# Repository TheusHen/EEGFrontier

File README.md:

# EEGFrontier V2

> [!CAUTION]
> **THIS BRANCH IS OUTDATED – DO NOT FABRICATE THIS BOARD!**
> The design files in this `v2` branch are outdated and contain known hardware issues. A new version is currently under active development. **Under no circumstances should you manufacture or order PCBs from this branch.** Please wait for the official update and release.

EEGFrontier is an open-source EEG acquisition platform built around Texas Instruments ADS1299 and the Seeed XIAO RP2040.

This repository includes:
- Hardware design files (KiCad)
- Firmware (PlatformIO / Arduino)
- Project assets and documentation images
- Host software (`Pendulum`)

## Current Status

This branch introduces the **V2 PCB** update:
- Migration to **ADS1299IPAGR** and **8 EEG channels**
- PCB rework focused on lower noise
- Curved routing for cleaner analog signal paths
- Revised GND strategy (less direct GND trace routing in sensitive analog areas)

Still pending on V2:
- BOM update
- Firmware update and validation for the new hardware revision

## V1 vs V2 Snapshot

| Topic | V1 | V2 |
|---|---|---|
| Analog front-end | ADS1299-4PAGR (4 channels) | ADS1299IPAGR (8 channels) |
| PCB routing style | Conventional routing | Curved tracks and analog cleanup |
| Noise-focused changes | Baseline | GND/routing revisions to reduce coupling and noise |

## Visual Comparison

### 3D View (Front)

| V1 | V2 |
|---|---|
|  |  |

### 3D View (Back)

| V1 | V2 |
|---|---|
|  |  |

### PCB Layout

| V1 | V2 |
|---|---|
|  |  |

### Schematic

| V1 | V2 |
|---|---|
|  |  |

## Project Concept

The board connects dry electrodes and streams real-time EEG data to a computer over USB for analysis and visualization.
The main objective is practical learning: open hardware + open firmware + transparent signal chain.

## Quick Start

1. Flash the firmware to the Seeed XIAO RP2040 using PlatformIO.
2. Connect the EEGFrontier board via USB.
3. Attach EEG electrodes (channels, REF, BIAS).
4. Open Pendulum or a serial monitor.
5. Start streaming with the `START` command.

## Hardware Highlights (V2)

- ADS1299IPAGR-based 8-channel EEG analog front-end
- Seeed XIAO RP2040 as main controller
- Input header for EEG channels + reference + bias
- Start button input (`BTN_START`)
- Status LEDs (power and stream/activity)
- Compact two-layer PCB with revised analog routing decisions

## Firmware Overview

The firmware in `firmware/` currently provides:
- ADS1299 initialization and register configuration
- DRDY interrupt-based sampling
- Binary streaming protocol (COBS + CRC16)
- CSV debug mode
- Serial commands for diagnostics and control
- Recovery logic for acquisition timeout
- Self-test and lead-off diagnostics

Note: firmware behavior and defaults still need full alignment with the V2 hardware revision.

## Firmware Build (PlatformIO)

```bash
cd firmware
pio run -e xiao_rp2040
```

Monitor (default baud rate `921600`):

```bash
cd firmware
pio device monitor -b 921600
```

## Serial Commands (Firmware)

- `HELP`
- `INFO`
- `STATS`
- `REGS`
- `START`
- `STOP`
- `MODE BIN`
- `MODE CSV`
- `REINIT`
- `TEST ON`
- `TEST OFF`
- `SELFTEST`
- `LOFF ON`
- `LOFF OFF`
- `LOFF STATUS`
- `PING`

## Technical Specifications

- Channels: 8 EEG channels + REF + BIAS (V2 target)
- ADC: 24-bit (ADS1299 family)
- Sampling rate: configurable (up to ADS1299 limits)
- Interface: USB (CDC)
- Power: USB 5V

## Repository Structure

- `firmware/` - PlatformIO firmware for XIAO RP2040 + ADS1299
- `assets/` - Images used in this README
- `bom/` - Bill of Materials and pricing references
- `EEGFrontier.kicad_sch` / `EEGFrontier.kicad_pcb` - KiCad project files
- `Pendulum/` - Host software suite (**OUTDATED for V2 / 8 channels**)

## Pendulum (OUTDATED)

Outdated status:
- The current `Pendulum` implementation is still aligned with the previous channel configuration.
- It needs to be updated to fully support the V2 hardware changes (8 channels via ADS1299IPAGR).

For now, `Pendulum/README.md` should be treated as historical reference until the 8-channel update is done.

## Manufacturing Recommendation

Fully hand-soldering this board is not recommended.

The design uses fine-pitch components and sensitive analog circuitry. Prefer full assembly from a professional PCB assembly service (for example, JLCPCB), then hand-solder only unavoidable missing parts if necessary.

## Safety and Protection

Important safety notice:

This device interfaces electrically with the human body and must be used with caution.

- This project does not include medical-grade isolation.
- Never connect it to mains-powered equipment without proper USB isolation.
- Always operate with a battery-powered computer or a biomedical USB isolator.
- Do not use if the board, cables, or electrodes are damaged.
- Do not use on individuals with implanted electronic devices (for example, pacemakers).
- This project is for research, education, and experimentation only.

The author assumes no responsibility for misuse, unsafe assembly, or unsafe operation.

## Medical Disclaimer

This project is not a medical device and is not intended for diagnosis, treatment, or clinical use.

Any produced data is experimental and for education/research use only.

## Known Limitations

- No medical-grade isolation
- No onboard battery
- Susceptible to motion artifacts with dry electrodes
- Requires external software for filtering and analysis (for example, Pendulum)
- V2 BOM and firmware migration are still in progress
- Pendulum host software is outdated and still pending migration to 8 channels

## License

This project is released under the MIT License.
See `LICENSE` for details.

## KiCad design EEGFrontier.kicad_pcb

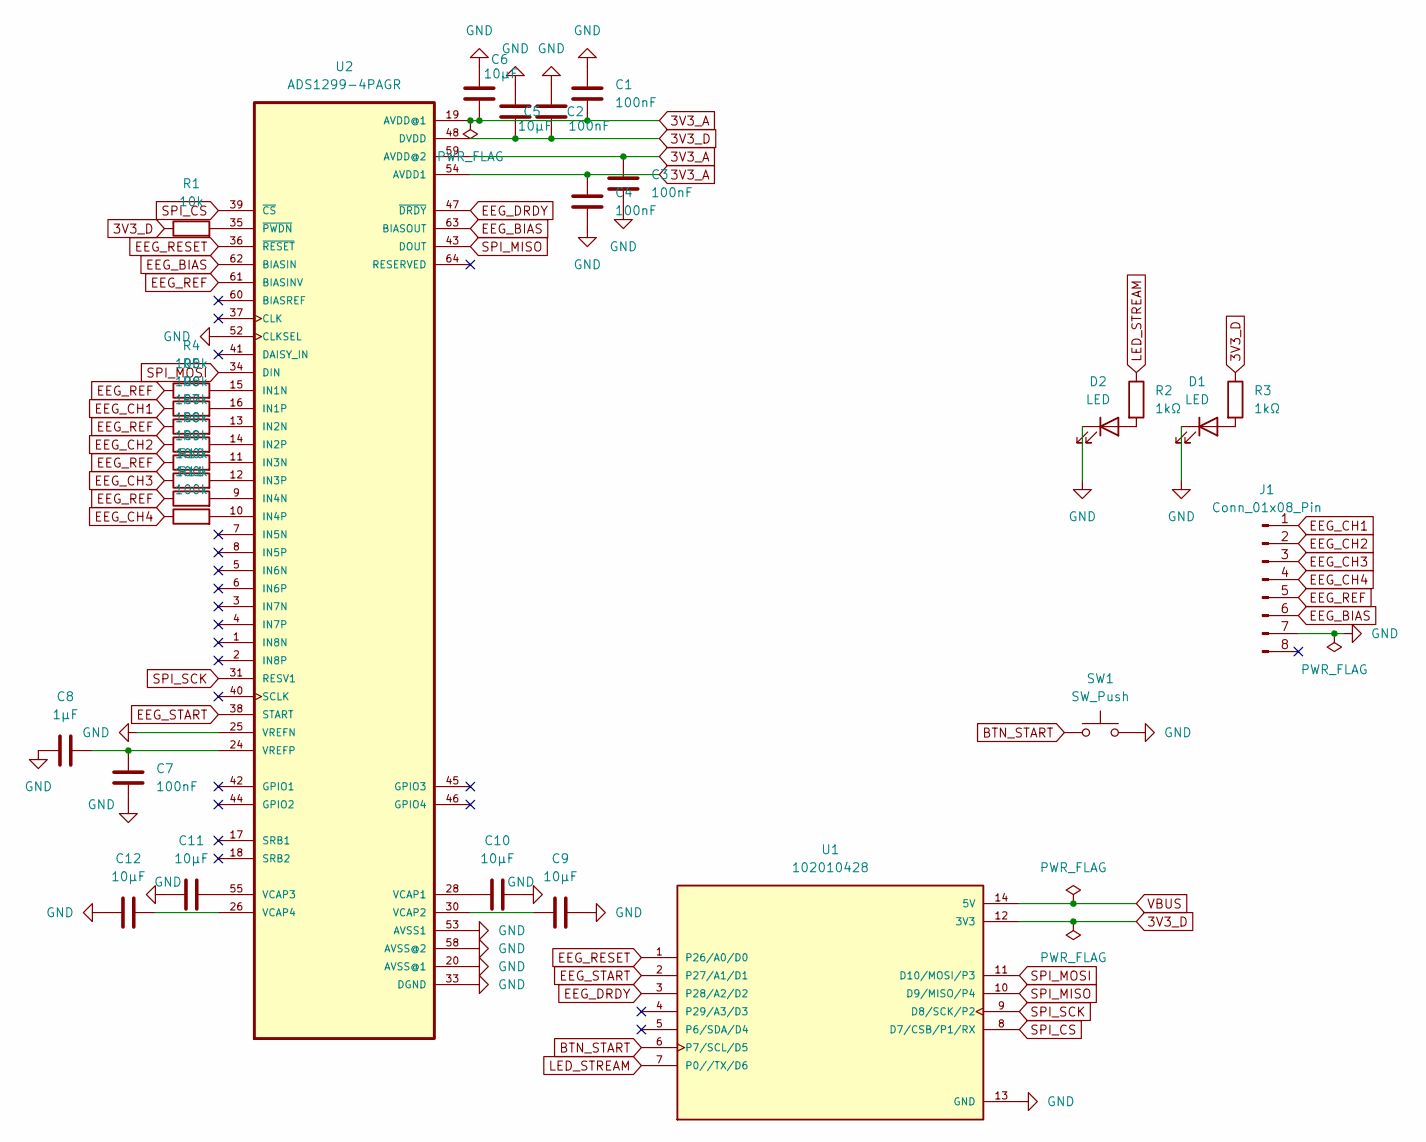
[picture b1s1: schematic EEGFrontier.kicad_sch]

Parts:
C1, C2, C3, C4, C7: 100nF; C_0603_1608Metric
C5, C6, C9, C10, C11, C12: 10µF; C_1206_3216Metric
C8: 1µF; C_0603_1608Metric
D1, D2: LED; LED_0805_2012Metric
J1: Conn_01x08_Pin; PinHeader_1x08_P2.54mm_Horizontal
R1: 10k; R_0805_2012Metric
R2, R3: 1kΩ; R_0805_2012Metric
R4, R5, R6, R7, R8, R9, R10, R11: 100k; R_0805_2012Metric
SW1: SW_Push; SW_Push_SPST_NO_Alps_SKRK
U1: 102010428; MODULE_102010428; PARTREV 1.3
U2: ADS1299-4PAGR; QFP50P1200X1200X120-64N

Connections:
3V3_A: C1.1, C3.2, C4.2, C6.1, U2.19 (AVDD@1), U2.21 (AVDD@1), U2.22 (AVDD@1), U2.54 (AVDD1), U2.56 (AVDD@1), U2.59 (AVDD@2)
3V3_D: C2.1, C5.1, R1.1, R3.1, U1.12 (3V3), U2.48 (DVDD), U2.50 (DVDD)
BTN_START: SW1.1, U1.6 (P7/SCL/D5)
EEG_BIAS: J1.6, U2.62 (BIASIN), U2.63 (BIASOUT)
EEG_CH1: J1.1, R5.1
EEG_CH2: J1.2, R7.1
EEG_CH3: J1.3, R9.1
EEG_CH4: J1.4, R11.1
EEG_DRDY: U1.3 (P28/A2/D2), U2.47 (~DRDY)
EEG_REF: J1.5, R4.1, R6.1, R8.1, R10.1, U2.61 (BIASINV)
EEG_RESET: U1.1 (P26/A0/D0), U2.36 (~RESET)
EEG_START: U1.2 (P27/A1/D1), U2.38 (START)
GND: C1.2, C2.2, C3.1, C4.1, C5.2, C6.2, C7.2, C8.2, C9.2, C10.2, C11.2, C12.2, D1.1 (K), D2.1 (K), J1.7, SW1.2, U1.13 (GND), U2.20 (AVSS@1), U2.23 (AVSS@1), U2.25 (VREFN), U2.32 (AVSS@1), U2.33 (DGND), U2.49 (DGND), U2.51 (DGND), U2.52 (CLKSEL), U2.53 (AVSS1), U2.57 (AVSS@1), U2.58 (AVSS@2)
LED_STREAM: R2.1, U1.7 (P0//TX/D6)
unnamed: D1.2 (A), R3.2
unnamed: D2.2 (A), R2.2
unnamed: R4.2, U2.15 (IN1N)
unnamed: R5.2, U2.16 (IN1P)
unnamed: R6.2, U2.13 (IN2N)
unnamed: R7.2, U2.14 (IN2P)
unnamed: R8.2, U2.11 (IN3N)
unnamed: R9.2, U2.12 (IN3P)
unnamed: R10.2, U2.9 (IN4N)
unnamed: R11.2, U2.10 (IN4P)
unnamed: C10.1, U2.28 (VCAP1)
unnamed: C9.1, U2.30 (VCAP2)
unnamed: C11.1, U2.55 (VCAP3)
unnamed: C12.1, U2.26 (VCAP4)
unnamed: C7.1, C8.1, U2.24 (VREFP)
unnamed: R1.2, U2.35 (~PWDN)
SPI_CS: U1.8 (D7/CSB/P1/RX), U2.39 (~CS)
SPI_MISO: U1.10 (D9/MISO/P4), U2.43 (DOUT)
SPI_MOSI: U1.11 (D10/MOSI/P3), U2.34 (DIN)
SPI_SCK: U1.9 (D8/SCK/P2), U2.31 (RESV1)
VBUS: U1.14 (5V)

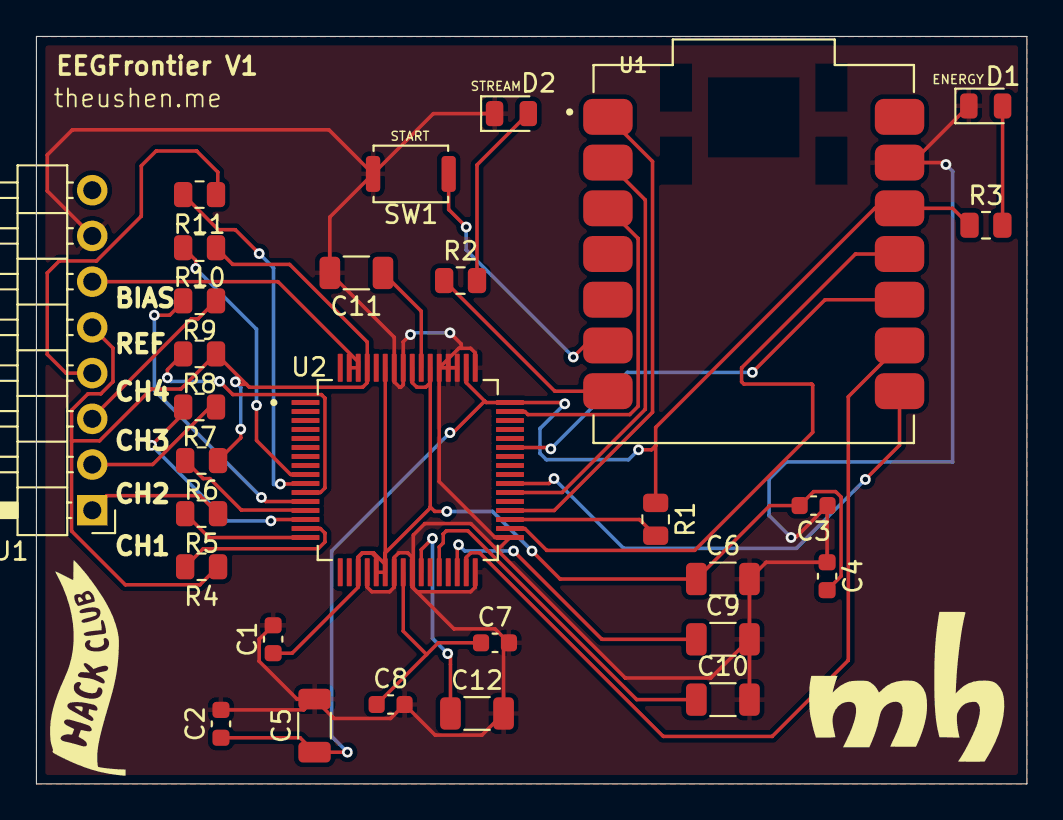
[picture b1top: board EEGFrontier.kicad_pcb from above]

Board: 2 copper layers, 55.0 x 41.5 mm, 29 parts (0 on the bottom side), 34 nets.

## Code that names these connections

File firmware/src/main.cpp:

#include <Arduino.h>
#include <SPI.h>

#include "ads1299_driver.h"
#include "fw_commands.h"
#include "fw_config.h"
#include "fw_protocol.h"
#include "fw_state.h"
#include "fw_tx.h"
#include "fw_watchdog.h"

namespace {

void blinkCode(uint8_t times, uint16_t onMs = 120) {
  for (uint8_t i = 0; i < times; i++) {
    digitalWrite(PIN_LED_STREAM, HIGH);
    delay(onMs);
    digitalWrite(PIN_LED_STREAM, LOW);
    delay(onMs);
  }
}

}  // namespace

void setup() {
  pinMode(PIN_EEG_RESET, OUTPUT);
  pinMode(PIN_EEG_START, OUTPUT);
  pinMode(PIN_SPI_CS, OUTPUT);
  pinMode(PIN_LED_STREAM, OUTPUT);

  pinMode(PIN_EEG_DRDY, INPUT_PULLUP);
  pinMode(PIN_BTN_START, INPUT_PULLUP);

  digitalWrite(PIN_SPI_CS, HIGH);
  digitalWrite(PIN_EEG_RESET, HIGH);
  digitalWrite(PIN_EEG_START, LOW);
  digitalWrite(PIN_LED_STREAM, LOW);

  Serial.begin(SERIAL_BAUD);
  txInit();

  // Give USB CDC a moment to enumerate without stalling forever on
  // battery-powered setups where nobody opens the port.
  uint32_t bootStart = millis();
  while (!Serial && static_cast<uint32_t>(millis() - bootStart) < 400) {
    delay(5);
  }

  SPI.setSCK(PIN_SPI_SCK);
  SPI.setTX(PIN_SPI_MOSI);
  SPI.setRX(PIN_SPI_MISO);
  SPI.begin();

  attachInterrupt(digitalPinToInterrupt(PIN_EEG_DRDY), onDrdyFalling, FALLING);

  fwWatchdogInit(2000);

  printLine("");
  printLine("# BOOT EEGFrontier_V2");
  printLine("# DEFAULT MODE BIN");
  printLine("# hardware_isolation=USB_to_EEG_SPI_and_power");
  printLine("# WARN research hardware; isolation is not IEC 60601-1 certified");
  printHelp();

  if (g_watchdogRebootDetected) {
    emitEventPacket(EVT_HELLO, 0x5242544CUL /*RBOT*/, g_recoveriesTotal, 0);
  }
  emitHelloPacket();
  bool ok = adsInitRobust();
  g_lastGoodFrameUs = micros();
  if (!ok) {
    blinkCode(2);
  }
  txService();
}

void loop() {
  fwWatchdogFeed();
  txService();
  handleSerialCommands();
  handleButton();

  if (g_streaming) {
    // Drain at most one frame per loop so commands stay responsive at
    // 500/1000 SPS. The DRDY flag coalesces overruns into missed counts.
    handleOneSampleFrame();
    txService();
  }

  recoverAdsIfNeeded();

  // Slow status blink while idle with lead-off or errors pending.
  static uint32_t lastIdleBlink = 0;
  if (!g_streaming) {
    uint32_t now = millis();
    if (static_cast<uint32_t>(now - lastIdleBlink) > 2000) {
      lastIdleBlink = now;
      if (!g_adsReady) {
        blinkCode(2, 80);
      }
    }
  }

  txService();
}

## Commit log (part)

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2026-02-26 Fixed plataform
2026-02-26 Refactor code structure for improved readability and maintainability
2026-02-26 Updated PCB images after changed the Header
2026-02-26 Add Gerber job file for EEGFrontier project with specifications and layer details
2026-02-27 Add extended version section to README
    Added extended version section with fixed header image.
2026-02-27 Update README to remove outdated diagrams
    Removed the old diagram and extended version section from the README.
2026-02-27 Rename diagram.png to old_diagram.png
2026-02-28 Add EEG processing and visualization components
    - Implemented mne_tools.py for converting sample records to MNE Raw format.
    - Created models.py to define data structures for sample, event, and error packets.
    - Developed pyqt_focus.py for a PyQt-based focus monitoring GUI with real-time EEG data visualization.
    - Added eflex_bridge.py to manage the EEG engine instance.
    - Introduced simulator.py to simulate EEG data packets for testing purposes.
    - Established a web dashboard in pendulum_web.py for live EEG data display and diagnostics.
2026-03-01 Add band-filtered EEG signal views and redesign dashboard UI
    - add reusable band-pass helpers with scipy/FFT fallback and expose ordered signal views\n- include per-band signal plot points in engine snapshots for raw/gamma/beta/alpha/theta/delta\n- refactor Re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
2026-03-01 Added electrode pin example(check web)
2026-03-01 Add uf2 submodule for firmware updates
2026-03-01 Improved README.md
2026-03-01 Clarify external software requirement for filtering and analysis in README.md
2026-03-20 feat(hw): launch EEGFrontier V2 with ADS1299IPAGR and 8-channel PCB update
    - migrate analog front-end from ADS1299-4PAGR (V1) to ADS1299IPAGR (V2)
    - expand hardware target from 4 EEG channels to 8 channels
    - apply PCB noise-reduction rework:
    - reduce direct GND trace routing in sensitive analog areas
    - adopt curved track routing for cleaner analog paths
    - update KiCad design artifacts (PCB/SCH) and generated fabrication outputs
2026-03-20 Revise README for BOM and Price Notes to V2
    Updated the Bill of Materials to reflect changes in component specifications and pricing for EEGFrontier V2.
2026-03-20 Remove concept/wiring comparison from README
    Removed the concept/wiring section from the README.
2026-04-30 Critical: Fixed float 3V3 #5
